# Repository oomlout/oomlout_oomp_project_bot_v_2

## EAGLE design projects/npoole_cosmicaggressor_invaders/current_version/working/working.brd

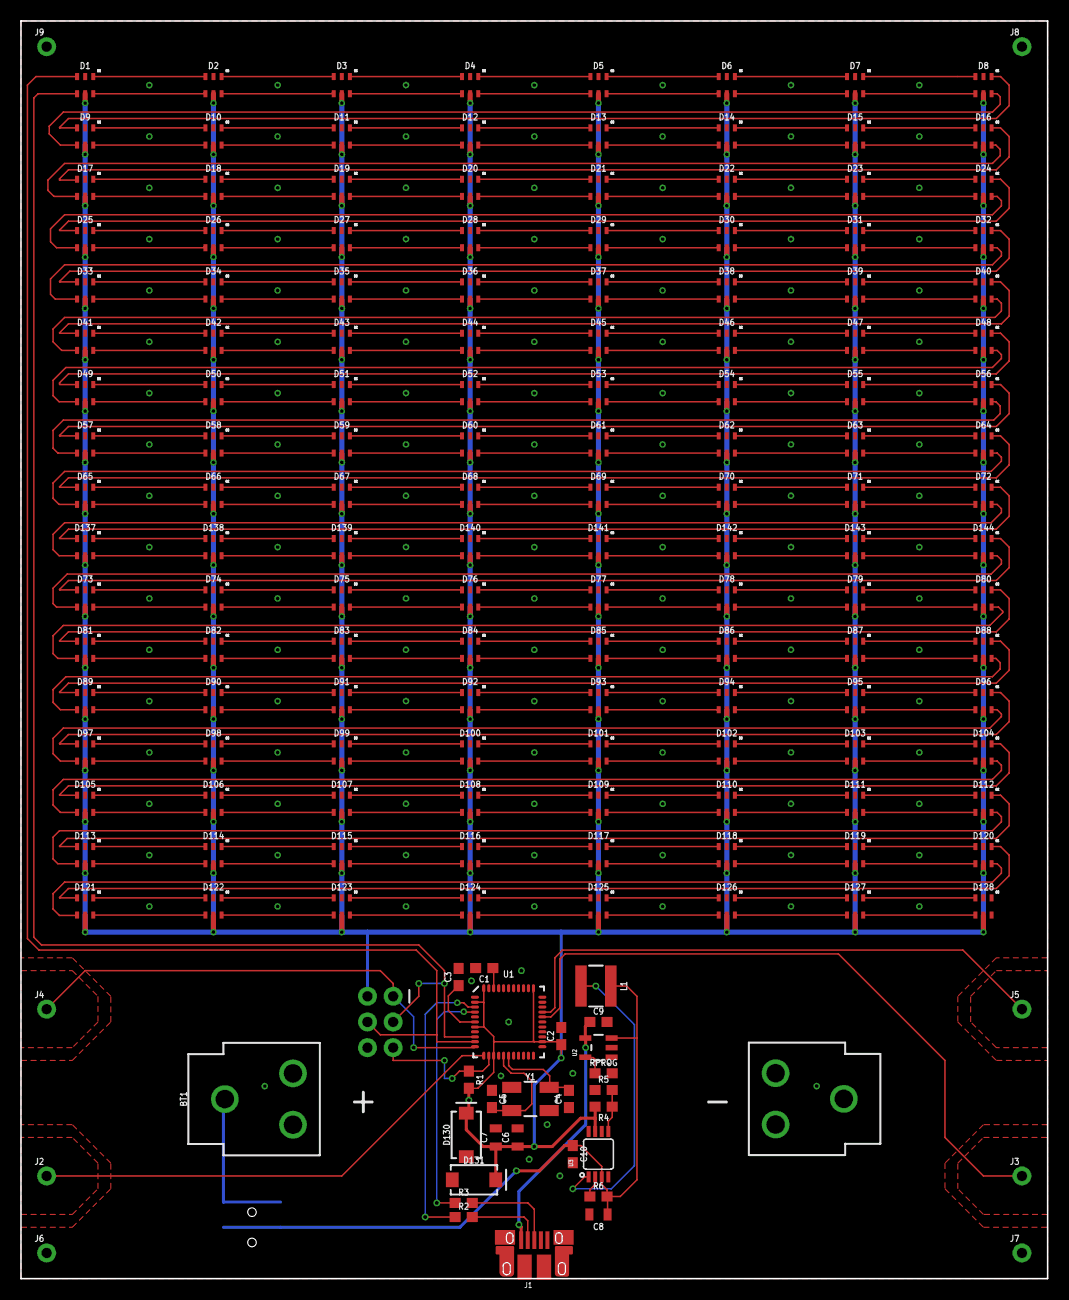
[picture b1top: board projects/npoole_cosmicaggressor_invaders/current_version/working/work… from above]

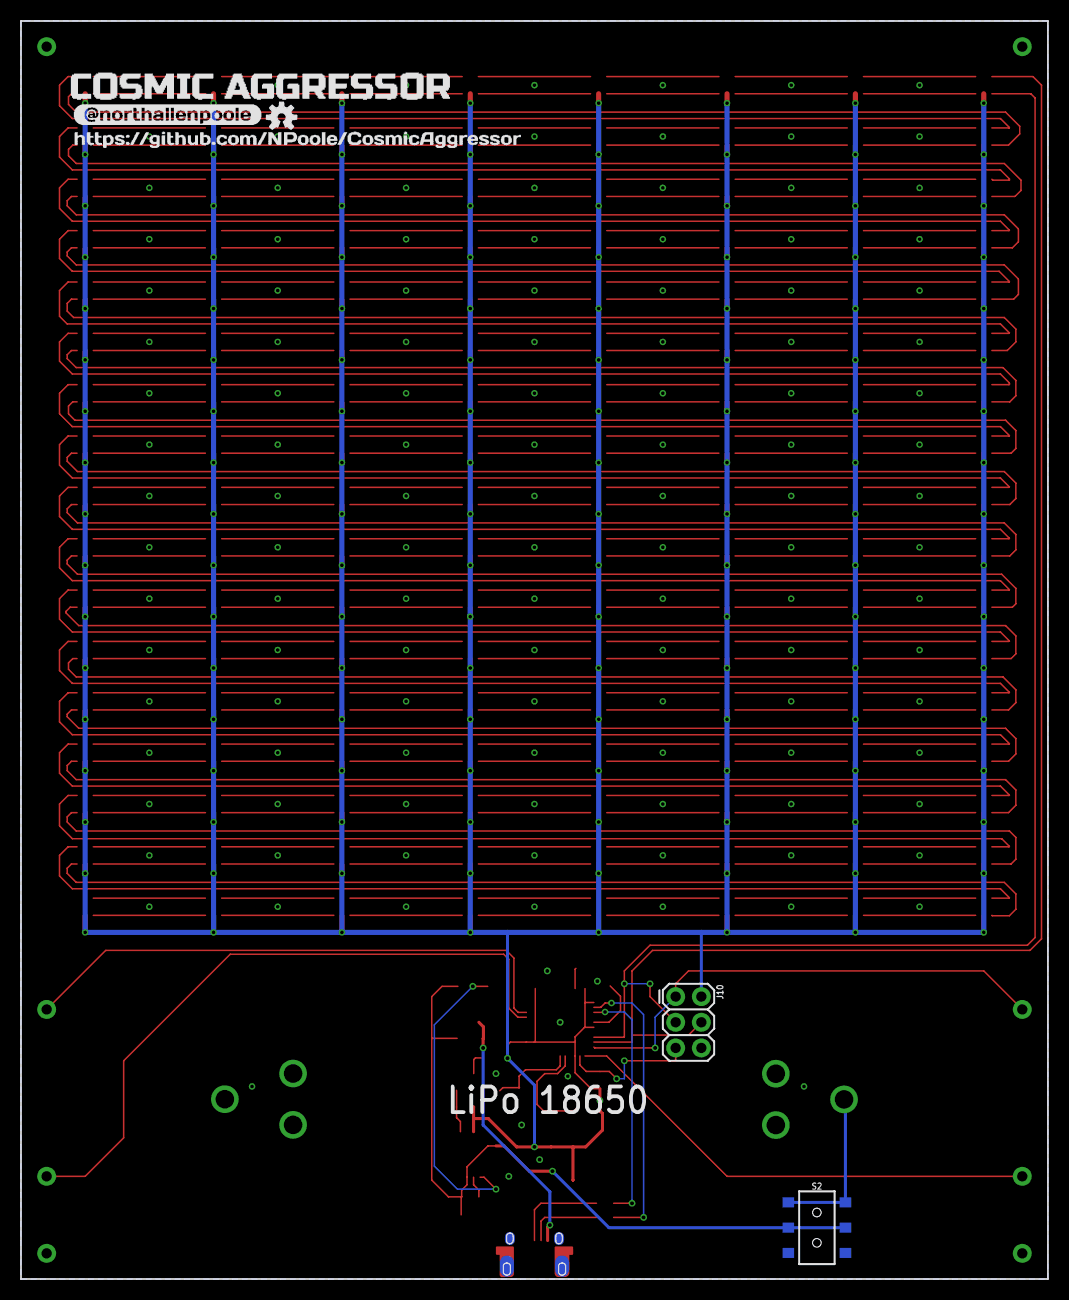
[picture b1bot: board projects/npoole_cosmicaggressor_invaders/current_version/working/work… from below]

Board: 2 copper layers, 101.6 x 124.5 mm, 176 parts (6 on the bottom side), 294 nets.

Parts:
BT1: BATTERY_18650-HOLDER
C1: 0.1uF; 0603
C2, C3: 1.0uF; 0603
C4, C5: 18pF; 0603
C6, C7, C8: 22uF; 0805
C9, C10: 4.7uF; 0603
D1, D2, D3, D4, D5, D6, D7, D8, D9, D10, D11, D12, D13, D14, D15, D16, D17, D18, D19, D20, D21, D22, D23, D24, D25, D26, D27, D28, D29, D30, D31, D32, D33, D34, D35, D36, D37, D38, D39, D40, D41, D42, D43, D44, D45, D46, D47, D48, D49, D50, D51, D52, D53, D54, D55, D56, D57, D58, D59, D60, D61, D62, D63, D64, D65, D66, D67, D68, D69, D70, D71, D72, D73, D74, D75, D76, D77, D78, D79, D80, D81, D82, D83, D84, D85, D86, D87, D88, D89, D90, D91, D92, D93, D94, D95, D96, D97, D98, D99, D100, D101, D102, D103, D104, D105, D106, D107, D108, D109, D110, D111, D112, D113, D114, D115, D116, D117, D118, D119, D120, D121, D122, D123, D124, D125, D126, D127, D128, D137, D138, D139, D140, D141, D142, D143, D144: APA102-2020
D130, D131: 3A/40V/500mV; SMA-DIODE
J1: USB-MICROB-PTH-MILL
J2, J3, J4, J5, J6, J7, J8, J9: 1X01NS_KIT
J10: AVR_SPI_PROG_3X2PTH; 2X3
L1: 2.2UH3A; INDUCTOR_4X4MM
R1: 10k; 0603@1
R2, R3: 22; 0603@1
R4, R6: 750K; 0603
R5: 100k; 0603
RPROG: 2.0k; 0603
S2: SWITCH_DPDT_SMD_AYZ0202
U1: 32U4; QFN-44-NOPAD_1:1-LESS_PASTE
U2: MCP73831; SOT23-5
U3: PAM2401; MSOP8
U$1: COSMIC_AGGRESSOR0
U$2: #NORTHALLENPOOLE1
U$3: HTTPS###GITHUB#COM#NPOOLE#COSMICAGGRESSOR2
U$4: OSHW-LOGO-S
Y1: 16MHz; CRYSTAL-SMD-5X3.2-4PAD

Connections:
5VIN: C9.1, J1.VBUS, U2.4
!RST: J10.5, R1.1, U1.13
D+: R3.1, U1.4
D-: R2.1, U1.3
EN: R6.1, U3.2
FIRE1: J2.1, U1.12
FIRE2: J3.1, U1.29
GND: BT1.GND@1, C1.2, C2.2, C3.2, C4.1, C5.1, C6.2, C7.2, C8.2, C9.2, C10.2, D1.GND, D2.GND, D3.GND, D4.GND, D5.GND, D6.GND, D7.GND, D8.GND, D9.GND, D10.GND, D11.GND, D12.GND, D13.GND, D14.GND, D15.GND, D16.GND, D17.GND, D18.GND, D19.GND, D20.GND, D21.GND, D22.GND, D23.GND, D24.GND, D25.GND, D26.GND, D27.GND, D28.GND, D29.GND, D30.GND, D31.GND, D32.GND, D33.GND, D34.GND, D35.GND, D36.GND, D37.GND, D38.GND, D39.GND, D40.GND, D41.GND, D42.GND, D43.GND, D44.GND, D45.GND, D46.GND, D47.GND, D48.GND, D49.GND, D50.GND, D51.GND, D52.GND, D53.GND, D54.GND, D55.GND, D56.GND, D57.GND, D58.GND, D59.GND, D60.GND, D61.GND, D62.GND, D63.GND, D64.GND, D65.GND, D66.GND, D67.GND, D68.GND, D69.GND, D70.GND, D71.GND, D72.GND, D73.GND, D74.GND, D75.GND, D76.GND, D77.GND, D78.GND, D79.GND, D80.GND, D81.GND, D82.GND, D83.GND, D84.GND, D85.GND, D86.GND, D87.GND, D88.GND, D89.GND, D90.GND, D91.GND, D92.GND, D93.GND, D94.GND, D95.GND, D96.GND, D97.GND, D98.GND, D99.GND, D100.GND, D101.GND, D102.GND, D103.GND, D104.GND, D105.GND, D106.GND, D107.GND, D108.GND, D109.GND, D110.GND, D111.GND, D112.GND, D113.GND, D114.GND, D115.GND, D116.GND, D117.GND, D118.GND, D119.GND, D120.GND, D121.GND, D122.GND, D123.GND, D124.GND, D125.GND, D126.GND, D127.GND, D128.GND, D130.A, D131.A, D137.GND, D138.GND, D139.GND, D140.GND, D141.GND, D142.GND, D143.GND, D144.GND, J1.GND, J1.SHIELD, J1.SHIELD2, J1.SHIELD3, J1.SHIELD4, J1.SHIELD5, J1.SHIELD6, J1.SHIELD7, J1.SHIELD8, J1.SHIELD9, J1.SHIELD10, J6.1, J7.1, J8.1, J9.1, J10.6, R5.1, RPROG.2, U1.5, U1.15, U1.23, U1.35, U1.43, U2.2, U3.4, U3.8
LEFT: J4.1, J10.1, U1.11
unnamed: D73.CKO, D74.CKI
unnamed: D73.SDO, D74.SDI
unnamed: D1.CKO, D2.CKI
unnamed: D1.SDO, D2.SDI
unnamed: D2.CKO, D3.CKI
unnamed: D2.SDO, D3.SDI
unnamed: D3.CKO, D4.CKI
unnamed: D3.SDO, D4.SDI
unnamed: D4.CKO, D5.CKI
unnamed: D4.SDO, D5.SDI
unnamed: D5.CKO, D6.CKI
unnamed: D5.SDO, D6.SDI
unnamed: D6.CKO, D7.CKI
unnamed: D6.SDO, D7.SDI
unnamed: D7.CKO, D8.CKI
unnamed: D7.SDO, D8.SDI
unnamed: D74.CKO, D75.CKI
unnamed: D74.SDO, D75.SDI
unnamed: D75.CKO, D76.CKI
unnamed: D75.SDO, D76.SDI
unnamed: D9.CKO, D10.CKI
unnamed: D9.SDO, D10.SDI
unnamed: D10.CKO, D11.CKI
unnamed: D10.SDO, D11.SDI
unnamed: D11.CKO, D12.CKI
unnamed: D11.SDO, D12.SDI
unnamed: D12.CKO, D13.CKI
unnamed: D12.SDO, D13.SDI
unnamed: D13.CKO, D14.CKI
unnamed: D13.SDO, D14.SDI
unnamed: D14.CKO, D15.CKI
unnamed: D14.SDO, D15.SDI
unnamed: D15.CKO, D16.CKI
unnamed: D15.SDO, D16.SDI
unnamed: D76.CKO, D77.CKI
unnamed: D76.SDO, D77.SDI
unnamed: D77.CKO, D78.CKI
unnamed: D77.SDO, D78.SDI
unnamed: D17.CKO, D18.CKI
unnamed: D17.SDO, D18.SDI
unnamed: D18.CKO, D19.CKI
unnamed: D18.SDO, D19.SDI
unnamed: D19.CKO, D20.CKI
unnamed: D19.SDO, D20.SDI
unnamed: D20.CKO, D21.CKI
unnamed: D20.SDO, D21.SDI
unnamed: D21.CKO, D22.CKI
unnamed: D21.SDO, D22.SDI
unnamed: D22.CKO, D23.CKI
unnamed: D22.SDO, D23.SDI
unnamed: D23.CKO, D24.CKI
unnamed: D23.SDO, D24.SDI
unnamed: D78.CKO, D79.CKI
unnamed: D78.SDO, D79.SDI
unnamed: D79.CKO, D80.CKI
unnamed: D79.SDO, D80.SDI
unnamed: D25.CKO, D26.CKI
unnamed: D25.SDO, D26.SDI
unnamed: D26.CKO, D27.CKI
unnamed: D26.SDO, D27.SDI
unnamed: D27.CKO, D28.CKI
unnamed: D27.SDO, D28.SDI
unnamed: D28.CKO, D29.CKI
unnamed: D28.SDO, D29.SDI
unnamed: D29.CKO, D30.CKI
unnamed: D29.SDO, D30.SDI
unnamed: D30.CKO, D31.CKI
unnamed: D30.SDO, D31.SDI
unnamed: D31.CKO, D32.CKI
unnamed: D31.SDO, D32.SDI
unnamed: D39.CKO, D40.CKI
unnamed: D39.SDO, D40.SDI
unnamed: D38.SDO, D39.SDI
unnamed: D38.CKO, D39.CKI
unnamed: D37.SDO, D38.SDI
unnamed: D37.CKO, D38.CKI
unnamed: D36.SDO, D37.SDI
unnamed: D36.CKO, D37.CKI
unnamed: D35.SDO, D36.SDI
unnamed: D35.CKO, D36.CKI
unnamed: D34.SDO, D35.SDI
unnamed: D34.CKO, D35.CKI
unnamed: D33.CKO, D34.CKI
unnamed: D33.SDO, D34.SDI
unnamed: D81.CKO, D82.CKI
unnamed: D81.SDO, D82.SDI
unnamed: D82.CKO, D83.CKI
unnamed: D82.SDO, D83.SDI
unnamed: D83.CKO, D84.CKI
unnamed: D83.SDO, D84.SDI
unnamed: D84.CKO, D85.CKI
unnamed: D84.SDO, D85.SDI
unnamed: D85.CKO, D86.CKI
unnamed: D85.SDO, D86.SDI
unnamed: D41.CKO, D42.CKI
unnamed: D41.SDO, D42.SDI
unnamed: D42.CKO, D43.CKI
unnamed: D42.SDO, D43.SDI
unnamed: D43.CKO, D44.CKI
unnamed: D43.SDO, D44.SDI
unnamed: D44.CKO, D45.CKI
unnamed: D44.SDO, D45.SDI
unnamed: D45.SDO, D46.SDI
unnamed: D45.CKO, D46.CKI
unnamed: D46.CKO, D47.CKI
unnamed: D46.SDO, D47.SDI
unnamed: D47.CKO, D48.CKI
unnamed: D47.SDO, D48.SDI
unnamed: D86.CKO, D87.CKI
unnamed: D86.SDO, D87.SDI
unnamed: D55.SDO, D56.SDI
unnamed: D55.CKO, D56.CKI
unnamed: D54.CKO, D55.CKI
unnamed: D54.SDO, D55.SDI
unnamed: D53.SDO, D54.SDI
unnamed: D53.CKO, D54.CKI
unnamed: D52.SDO, D53.SDI
unnamed: D52.CKO, D53.CKI
unnamed: D51.SDO, D52.SDI
unnamed: D51.CKO, D52.CKI
unnamed: D50.CKO, D51.CKI
unnamed: D50.SDO, D51.SDI
unnamed: D49.SDO, D50.SDI
unnamed: D49.CKO, D50.CKI
unnamed: D87.CKO, D88.CKI
unnamed: D87.SDO, D88.SDI
unnamed: D89.CKO, D90.CKI
unnamed: D89.SDO, D90.SDI
unnamed: D57.CKO, D58.CKI
unnamed: D57.SDO, D58.SDI
unnamed: D58.SDO, D59.SDI
unnamed: D58.CKO, D59.CKI
unnamed: D59.CKO, D60.CKI
unnamed: D59.SDO, D60.SDI
unnamed: D60.CKO, D61.CKI
unnamed: D60.SDO, D61.SDI
unnamed: D61.CKO, D62.CKI
unnamed: D61.SDO, D62.SDI
unnamed: D62.SDO, D63.SDI
unnamed: D62.CKO, D63.CKI
unnamed: D63.CKO, D64.CKI
unnamed: D63.SDO, D64.SDI
unnamed: D90.CKO, D91.CKI
unnamed: D90.SDO, D91.SDI
unnamed: D91.CKO, D92.CKI
unnamed: D91.SDO, D92.SDI
unnamed: D65.CKO, D66.CKI
unnamed: D65.SDO, D66.SDI
unnamed: D66.CKO, D67.CKI
unnamed: D66.SDO, D67.SDI
unnamed: D67.CKO, D68.CKI
unnamed: D67.SDO, D68.SDI
unnamed: D68.CKO, D69.CKI
unnamed: D68.SDO, D69.SDI
unnamed: D69.CKO, D70.CKI
unnamed: D69.SDO, D70.SDI
unnamed: D70.CKO, D71.CKI
unnamed: D70.SDO, D71.SDI
unnamed: D71.CKO, D72.CKI
unnamed: D71.SDO, D72.SDI
unnamed: D137.CKO, D138.CKI
unnamed: D137.SDO, D138.SDI
unnamed: D92.CKO, D93.CKI
unnamed: D92.SDO, D93.SDI
unnamed: D93.CKO, D94.CKI
unnamed: D93.SDO, D94.SDI
unnamed: D94.CKO, D95.CKI
unnamed: D94.SDO, D95.SDI
unnamed: D95.CKO, D96.CKI
unnamed: D95.SDO, D96.SDI
unnamed: D97.CKO, D98.CKI
unnamed: D97.SDO, D98.SDI
unnamed: D98.CKO, D99.CKI
unnamed: D98.SDO, D99.SDI
unnamed: D99.CKO, D100.CKI
unnamed: D99.SDO, D100.SDI
unnamed: D100.CKO, D101.CKI
unnamed: D100.SDO, D101.SDI
unnamed: D101.CKO, D102.CKI
unnamed: D101.SDO, D102.SDI
unnamed: D102.CKO, D103.CKI
unnamed: D102.SDO, D103.SDI
unnamed: D103.CKO, D104.CKI
unnamed: D103.SDO, D104.SDI
unnamed: D111.CKO, D112.CKI
unnamed: D111.SDO, D112.SDI
unnamed: D110.SDO, D111.SDI
unnamed: D110.CKO, D111.CKI
unnamed: D109.SDO, D110.SDI
unnamed: D109.CKO, D110.CKI
unnamed: D108.SDO, D109.SDI
unnamed: D108.CKO, D109.CKI
unnamed: D107.SDO, D108.SDI
unnamed: D107.CKO, D108.CKI
unnamed: D106.SDO, D107.SDI
unnamed: D106.CKO, D107.CKI
unnamed: D105.CKO, D106.CKI
unnamed: D105.SDO, D106.SDI
unnamed: D113.CKO, D114.CKI
unnamed: D113.SDO, D114.SDI
unnamed: D114.CKO, D115.CKI
unnamed: D114.SDO, D115.SDI
unnamed: D115.CKO, D116.CKI
unnamed: D115.SDO, D116.SDI
unnamed: D116.CKO, D117.CKI
unnamed: D116.SDO, D117.SDI
unnamed: D117.SDO, D118.SDI
unnamed: D117.CKO, D118.CKI
unnamed: D118.CKO, D119.CKI
unnamed: D118.SDO, D119.SDI
unnamed: D119.CKO, D120.CKI
unnamed: D119.SDO, D120.SDI
unnamed: D127.SDO, D128.SDI
unnamed: D127.CKO, D128.CKI
unnamed: D126.CKO, D127.CKI
unnamed: D126.SDO, D127.SDI
unnamed: D125.SDO, D126.SDI
unnamed: D125.CKO, D126.CKI
unnamed: D124.SDO, D125.SDI
unnamed: D124.CKO, D125.CKI
unnamed: D123.SDO, D124.SDI
unnamed: D123.CKO, D124.CKI
unnamed: D122.CKO, D123.CKI
unnamed: D122.SDO, D123.SDI
unnamed: D121.SDO, D122.SDI
unnamed: D121.CKO, D122.CKI
unnamed: C1.1, U1.42
unnamed: C4.2, U1.17, Y1.3
unnamed: C5.2, U1.16, Y1.1
unnamed: C3.1, U1.6
unnamed: RPROG.1, U2.5
unnamed: J1.D+, R3.2
unnamed: J1.D-, R2.2
unnamed: R4.1, R5.2, U3.5
unnamed: L1.P$2, U3.1
unnamed: BT1.PWR@1, S2.1, S2.4
unnamed: D138.CKO, D139.CKI
unnamed: D138.SDO, D139.SDI
unnamed: D139.CKO, D140.CKI
unnamed: D139.SDO, D140.SDI
unnamed: D140.CKO, D141.CKI
unnamed: D140.SDO, D141.SDI
unnamed: D141.CKO, D142.CKI
unnamed: D141.SDO, D142.SDI
unnamed: D142.CKO, D143.CKI
unnamed: D142.SDO, D143.SDI
unnamed: D143.CKO, D144.CKI
unnamed: D143.SDO, D144.SDI
R1CK: D1.CKI, J10.3, U1.9
R1DA: D1.SDI, J10.4, U1.10
R2CK: D8.CKO, D9.CKI
R2DA: D8.SDO, D9.SDI
R3CK: D16.CKO, D17.CKI
R3DA: D16.SDO, D17.SDI
R4CK: D24.CKO, D25.CKI
R4DA: D24.SDO, D25.SDI
R5CK: D32.CKO, D33.CKI
R5DA: D32.SDO, D33.SDI
R6CK: D40.CKO, D41.CKI
R6DA: D40.SDO, D41.SDI
R7CK: D48.CKO, D49.CKI
R7DA: D48.SDO, D49.SDI
R8CK: D56.CKO, D57.CKI
R8DA: D56.SDO, D57.SDI
R9CK: D64.CKO, D65.CKI
R9DA: D64.SDO, D65.SDI
R10CK: D72.CKO, D137.CKI
R10DA: D72.SDO, D137.SDI
R11CK: D73.CKI, D144.CKO
R11DA: D73.SDI, D144.SDO
R12CK: D80.CKO, D81.CKI
R12DA: D80.SDO, D81.SDI
R13CK: D88.CKO, D89.CKI
R13DA: D88.SDO, D89.SDI
R14CK: D96.CKO, D97.CKI
R14DA: D96.SDO, D97.SDI
R15CK: D104.CKO, D105.CKI
R15DA: D104.SDO, D105.SDI
R16CK: D112.CKO, D113.CKI
R16DA: D112.SDO, D113.SDI
R17CK: D120.CKO, D121.CKI
R17DA: D120.SDO, D121.SDI
RIGHT: J5.1, U1.30
VBATT: C8.1, C10.1, L1.P$1, R6.2, S2.2, S2.5, U2.3, U3.3
VCC: C2.1, C6.1, C7.1, D1.VDD, D2.VDD, D3.VDD, D4.VDD, D5.VDD, D6.VDD, D7.VDD, D8.VDD, D9.VDD, D10.VDD, D11.VDD, D12.VDD, D13.VDD, D14.VDD, D15.VDD, D16.VDD, D17.VDD, D18.VDD, D19.VDD, D20.VDD, D21.VDD, D22.VDD, D23.VDD, D24.VDD, D25.VDD, D26.VDD, D27.VDD, D28.VDD, D29.VDD, D30.VDD, D31.VDD, D32.VDD, D33.VDD, D34.VDD, D35.VDD, D36.VDD, D37.VDD, D38.VDD, D39.VDD, D40.VDD, D41.VDD, D42.VDD, D43.VDD, D44.VDD, D45.VDD, D46.VDD, D47.VDD, D48.VDD, D49.VDD, D50.VDD, D51.VDD, D52.VDD, D53.VDD, D54.VDD, D55.VDD, D56.VDD, D57.VDD, D58.VDD, D59.VDD, D60.VDD, D61.VDD, D62.VDD, D63.VDD, D64.VDD, D65.VDD, D66.VDD, D67.VDD, D68.VDD, D69.VDD, D70.VDD, D71.VDD, D72.VDD, D73.VDD, D74.VDD, D75.VDD, D76.VDD, D77.VDD, D78.VDD, D79.VDD, D80.VDD, D81.VDD, D82.VDD, D83.VDD, D84.VDD, D85.VDD, D86.VDD, D87.VDD, D88.VDD, D89.VDD, D90.VDD, D91.VDD, D92.VDD, D93.VDD, D94.VDD, D95.VDD, D96.VDD, D97.VDD, D98.VDD, D99.VDD, D100.VDD, D101.VDD, D102.VDD, D103.VDD, D104.VDD, D105.VDD, D106.VDD, D107.VDD, D108.VDD, D109.VDD, D110.VDD, D111.VDD, D112.VDD, D113.VDD, D114.VDD, D115.VDD, D116.VDD, D117.VDD, D118.VDD, D119.VDD, D120.VDD, D121.VDD, D122.VDD, D123.VDD, D124.VDD, D125.VDD, D126.VDD, D127.VDD, D128.VDD, D130.C, D131.C, D137.VDD, D138.VDD, D139.VDD, D140.VDD, D141.VDD, D142.VDD, D143.VDD, D144.VDD, J10.2, R1.2, R4.2, U1.2, U1.7, U1.14, U1.24, U1.34, U1.44, U3.7

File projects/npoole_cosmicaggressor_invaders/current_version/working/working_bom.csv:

"Id";"Designator";"Footprint";"Quantity";"Designation";"Supplier and ref";
1;"D72,D84,D8,D46,D67,D22,D29,D92,D126,D20,D68,D66,D52,D87,D108,D99,D95,D2,D57,D100,D127,D120,D117,D38,D102,D137,D31,D61,D17,D3,D65,D121,D37,D30,D85,D103,D98,D33,D140,D79,D41,D1,D81,D77,D40,D11,D75,D19,D47,D74,D62,D49,D93,D128,D109,D141,D143,D42,D56,D54,D71,D115,D78,D111,D124,D114,D110,D50,D144,D24,D26,D5,D107,D35,D4,D76,D43,D28,D7,D104,D45,D101,D63,D90,D122,D60,D51,D15,D55,D16,D116,D48,D39,D80,D34,D23,D32,D123,D112,D12,D96,D105,D10,D142,D58,D113,D9,D25,D125,D106,D94,D53,D86,D139,D36,D118,D18,D44,D13,D64,D73,D59,D138,D69,D21,D6,D27,D82,D70,D119,D91,D89,D97,D88,D83,D14";"APA102-2020";136;"APA102-2020";;;
2;"C9,C10";"0603";2;"4.7uF";;;
3;"U2";"SOT23-5";1;"MCP73831";;;
4;"R3,R2";"0603@1";2;"22";;;
5;"Y1";"CRYSTAL-SMD-5X3.2-4PAD";1;"16MHz";;;
6;"R1";"0603@1";1;"10k";;;
7;"BT1";"BATTERY_18650-HOLDER";1;"";;;
8;"J9,J6,J5,J8,J4,J7,J2,J3";"1X01NS_KIT";8;"";;;
9;"D131,D130";"SMA-DIODE";2;"3A/40V/500mV";;;
10;"C2,C3";"0603";2;"1.0uF";;;
11;"C8,C6,C7";"0805";3;"22uF";;;
12;"C4,C5";"0603";2;"18pF";;;
13;"R6,R4";"0603";2;"750K";;;
14;"RPROG0";"0603";1;"2.0k";;;
15;"R5";"0603";1;"100k";;;
16;"C1";"0603";1;"0.1uF";;;
17;"U3";"MSOP8";1;"PAM2401";;;
18;"L1";"INDUCTOR_4X4MM";1;"2.2UH3A";;;
19;"J1";"USB-MICROB-PTH-MILL";1;"";;;
20;"U1";"QFN-44-NOPAD_1_1-LESS_PASTE";1;"32U4";;;
21;"S2";"SWITCH_DPDT_SMD_AYZ0202";1;"";;;
22;"U$1";"COSMIC_AGGRESSOR0";1;"";;;
23;"J10";"2X3";1;"AVR_SPI_PROG_3X2PTH";;;
24;"U$2";"#NORTHALLENPOOLE1";1;"";;;
25;"U$4";"OSHW-LOGO-S";1;"";;;
26;"U$3";"HTTPS###GITHUB#COM#NPOOLE#COSMICAGGRESSOR2";1;"";;;

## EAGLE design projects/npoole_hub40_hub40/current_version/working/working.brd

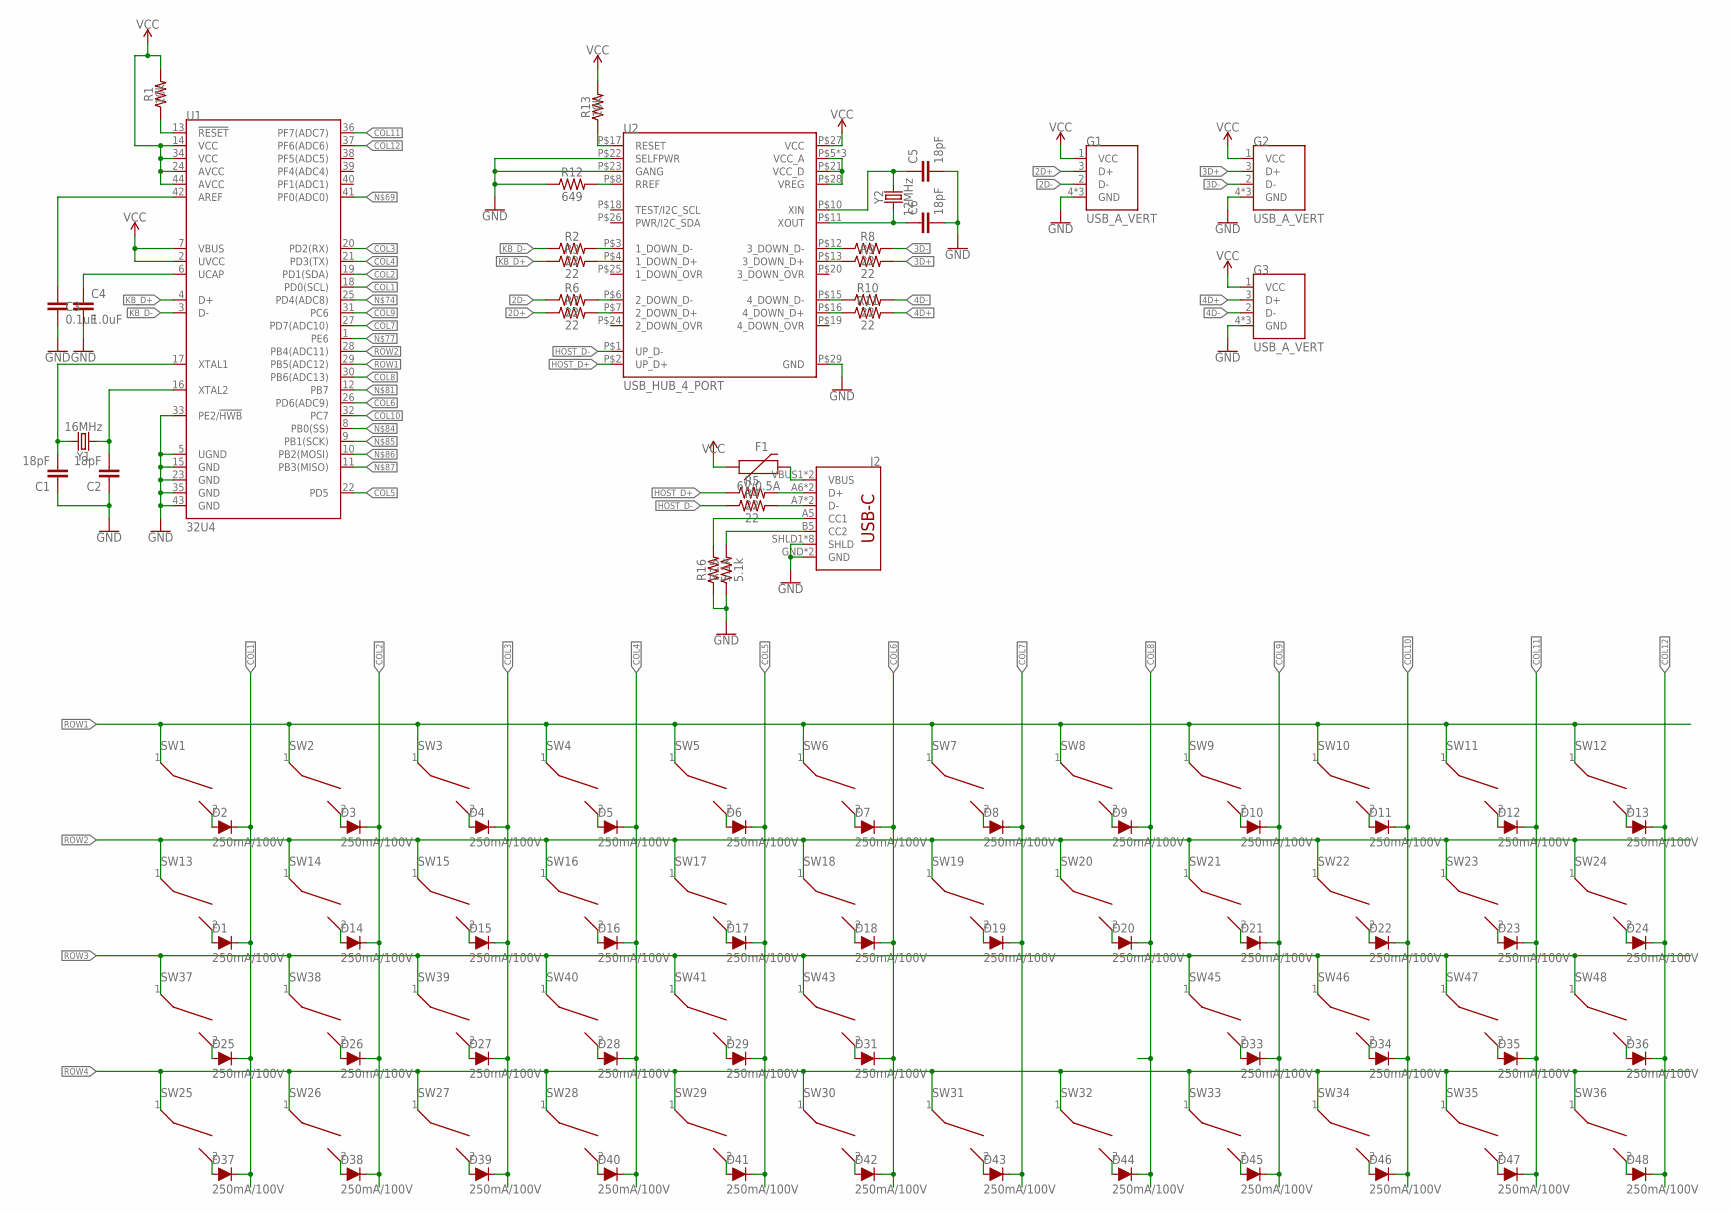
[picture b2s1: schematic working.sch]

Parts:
C1, C2, C5, C6: 18pF; 0603
C3: 0.1uF; 0603
C4: 1.0uF; 0603
D1, D2, D3, D4, D5, D6, D7, D8, D9, D10, D11, D12, D13, D14, D15, D16, D17, D18, D19, D20, D21, D22, D23, D24, D25, D26, D27, D28, D29, D31, D33, D34, D35, D36, D37, D38, D39, D40, D41, D42, D43, D44, D45, D46, D47, D48: 250mA/100V; SOD-323
F1: 6V/0.5A; 1206
G1, G2, G3: USB_A_VERT
J2: USB_C2-LAYER; USB-C-16P
R1, R13: 10k; 0603
R2, R3, R4, R5, R6, R7, R8, R9, R10, R11: 22; 0603
R12: 649; 0603
R15, R16: 5.1k; 0603
SW1, SW2, SW3, SW4, SW5, SW6, SW7, SW8, SW9, SW10, SW11, SW12, SW13, SW14, SW15, SW16, SW17, SW18, SW19, SW20, SW21, SW22, SW23, SW24, SW25, SW26, SW27, SW28, SW29, SW30, SW31, SW32, SW33, SW34, SW35, SW36, SW37, SW38, SW39, SW40, SW41, SW43, SW45, SW46, SW47, SW48: CHERRY_MX_WITH_FIXING_PINS; MX1A-XXNW
U1: 32U4; QFN-44-NOPAD_1:1
U2: USB_HUB_4_PORT; QFN-28-5MM-1:1
Y1: 16MHz; CRYSTAL-SMD-5X3.2-4PAD
Y2: 12MHz; CRYSTAL-SMD-5X3.2-4PAD

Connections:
2D+: G1.3 (D+), R7.1
2D-: G1.2 (D-), R6.1
3D+: G2.3 (D+), R9.2
3D-: G2.2 (D-), R8.2
4D+: G3.3 (D+), R11.2
4D-: G3.2 (D-), R10.2
COL1: D1.C, D2.C, D25.C, D37.C, U1.18 (PD0(SCL))
COL2: D3.C, D14.C, D26.C, D38.C, U1.19 (PD1(SDA))
COL3: D4.C, D15.C, D27.C, D39.C, U1.20 (PD2(RX))
COL4: D5.C, D16.C, D28.C, D40.C, U1.21 (PD3(TX))
COL5: D6.C, D17.C, D29.C, D41.C, U1.22 (PD5)
COL6: D7.C, D18.C, D31.C, D42.C, U1.26 (PD6(ADC9))
COL7: D8.C, D19.C, D43.C, U1.27 (PD7(ADC10))
COL8: D9.C, D20.C, D44.C, U1.30 (PB6(ADC13))
COL9: D10.C, D21.C, D33.C, D45.C, U1.31 (PC6)
COL10: D11.C, D22.C, D34.C, D46.C, U1.32 (PC7)
COL11: D12.C, D23.C, D35.C, D47.C, U1.36 (PF7(ADC7))
COL12: D13.C, D24.C, D36.C, D48.C, U1.37 (PF6(ADC6))
GND: C1.1, C2.1, C3.2, C4.2, C5.2, C6.2, G1.4 (GND), G1.SHIELD_1 (GND), G1.SHIELD_2 (GND), G2.4 (GND), G2.SHIELD_1 (GND), G2.SHIELD_2 (GND), G3.4 (GND), G3.SHIELD_1 (GND), G3.SHIELD_2 (GND), J2.GND, J2.GND2 (GND), J2.SHLD1 (SHLD), J2.SHLD2 (SHLD), J2.SHLD3 (SHLD), J2.SHLD4 (SHLD), J2.SHLD5 (SHLD), J2.SHLD6 (SHLD), J2.SHLD7 (SHLD), J2.SHLD8 (SHLD), R12.1, R15.1, R16.1, U1.5 (UGND), U1.15 (GND), U1.23 (GND), U1.33 (PE2/!HWB), U1.35 (GND), U1.43 (GND), U2.P$22 (SELFPWR), U2.P$23 (GANG), U2.P$29 (GND)
HOST-: J2.A7 (D-), J2.B7 (D-), R4.2
HOST_D+: R5.1, U2.P$2 (UP_D+)
HOST_D-: R4.1, U2.P$1 (UP_D-)
KBD+: R3.2, U2.P$4 (1_DOWN_D+)
KBD-: R2.2, U2.P$3 (1_DOWN_D-)
KB_D+: R3.1, U1.4 (D+)
KB_D-: R2.1, U1.3 (D-)
unnamed: D2.A, SW1.2
unnamed: D3.A, SW2.2
unnamed: D4.A, SW3.2
unnamed: D5.A, SW4.2
unnamed: D6.A, SW5.2
unnamed: D7.A, SW6.2
unnamed: D8.A, SW7.2
unnamed: D9.A, SW8.2
unnamed: D10.A, SW9.2
unnamed: D11.A, SW10.2
unnamed: D12.A, SW11.2
unnamed: D13.A, SW12.2
unnamed: D1.A, SW13.2
unnamed: D25.A, SW37.2
unnamed: D37.A, SW25.2
unnamed: D38.A, SW26.2
unnamed: D26.A, SW38.2
unnamed: D14.A, SW14.2
unnamed: D15.A, SW15.2
unnamed: D16.A, SW16.2
unnamed: D28.A, SW40.2
unnamed: D27.A, SW39.2
unnamed: D39.A, SW27.2
unnamed: D40.A, SW28.2
unnamed: D41.A, SW29.2
unnamed: D42.A, SW30.2
unnamed: D29.A, SW41.2
unnamed: D17.A, SW17.2
unnamed: D18.A, SW18.2
unnamed: J2.A6 (D+), J2.B6 (D+), R5.2
unnamed: D43.A, SW31.2
unnamed: D31.A, SW43.2
unnamed: D19.A, SW19.2
unnamed: D23.A, SW23.2
unnamed: D22.A, SW22.2
unnamed: D21.A, SW21.2
unnamed: D20.A, SW20.2
unnamed: J2.A5 (CC1), R16.2
unnamed: D33.A, SW45.2
unnamed: D34.A, SW46.2
unnamed: D35.A, SW47.2
unnamed: D36.A, SW48.2
unnamed: D24.A, SW24.2
unnamed: D48.A, SW36.2
unnamed: D47.A, SW35.2
unnamed: D46.A, SW34.2
unnamed: D45.A, SW33.2
unnamed: D44.A, SW32.2
unnamed: R1.1, U1.13 (!RESET)
unnamed: C3.1, U1.42 (AREF)
unnamed: C1.2, U1.17 (XTAL1), Y1.3 (2)
unnamed: C2.2, U1.16 (XTAL2), Y1.1
unnamed: C4.1, U1.6 (UCAP)
unnamed: R6.2, U2.P$6 (2_DOWN_D-)
unnamed: U2.P$5 (VCC_A), U2.P$9 (VCC_A), U2.P$14 (VCC_A), U2.P$21 (VCC_D), U2.P$28 (VREG)
unnamed: R7.2, U2.P$7 (2_DOWN_D+)
unnamed: R8.1, U2.P$12 (3_DOWN_D-)
unnamed: R9.1, U2.P$13 (3_DOWN_D+)
unnamed: R10.1, U2.P$15 (4_DOWN_D-)
unnamed: R11.1, U2.P$16 (4_DOWN_D+)
unnamed: C5.1, U2.P$10 (XIN), Y2.3 (2)
unnamed: C6.1, U2.P$11 (XOUT), Y2.1
unnamed: R13.1, U2.P$17 (RESET)
unnamed: F1.2, J2.VBUS1 (VBUS), J2.VBUS2 (VBUS)
unnamed: R12.2, U2.P$8 (RREF)
unnamed: J2.B5 (CC2), R15.2
ROW1: SW1.1, SW2.1, SW3.1, SW4.1, SW5.1, SW6.1, SW7.1, SW8.1, SW9.1, SW10.1, SW11.1, SW12.1, U1.29 (PB5(ADC12))
ROW2: SW13.1, SW14.1, SW15.1, SW16.1, SW17.1, SW18.1, SW19.1, SW20.1, SW21.1, SW22.1, SW23.1, SW24.1, U1.28 (PB4(ADC11))
ROW3: SW37.1, SW38.1, SW39.1, SW40.1, SW41.1, SW43.1, SW45.1, SW46.1, SW47.1, SW48.1
ROW4: SW25.1, SW26.1, SW27.1, SW28.1, SW29.1, SW30.1, SW31.1, SW32.1, SW33.1, SW34.1, SW35.1, SW36.1
VCC: F1.1, G1.1 (VCC), G2.1 (VCC), G3.1 (VCC), R1.2, R13.2, U1.2 (UVCC), U1.7 (VBUS), U1.14 (VCC), U1.24 (AVCC), U1.34 (VCC), U1.44 (AVCC), U2.P$27 (VCC)

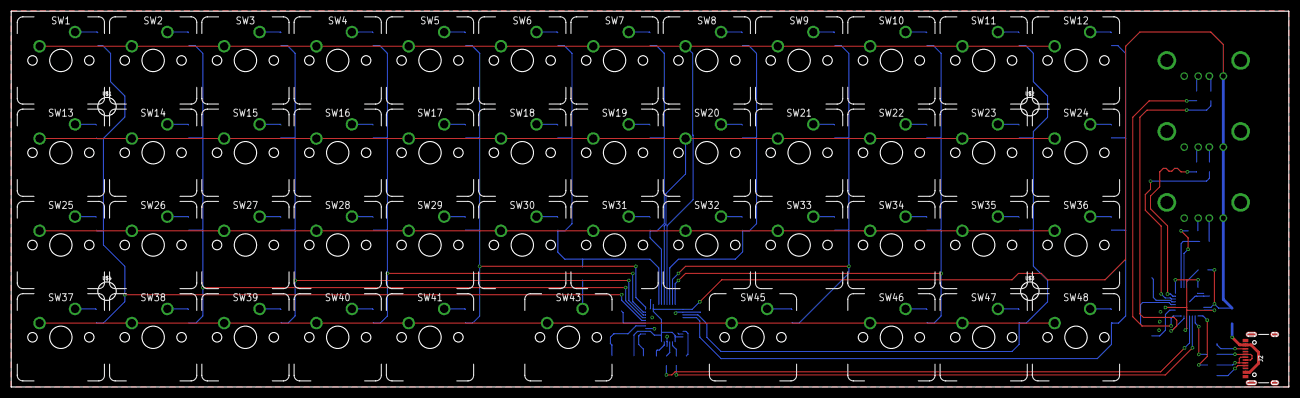
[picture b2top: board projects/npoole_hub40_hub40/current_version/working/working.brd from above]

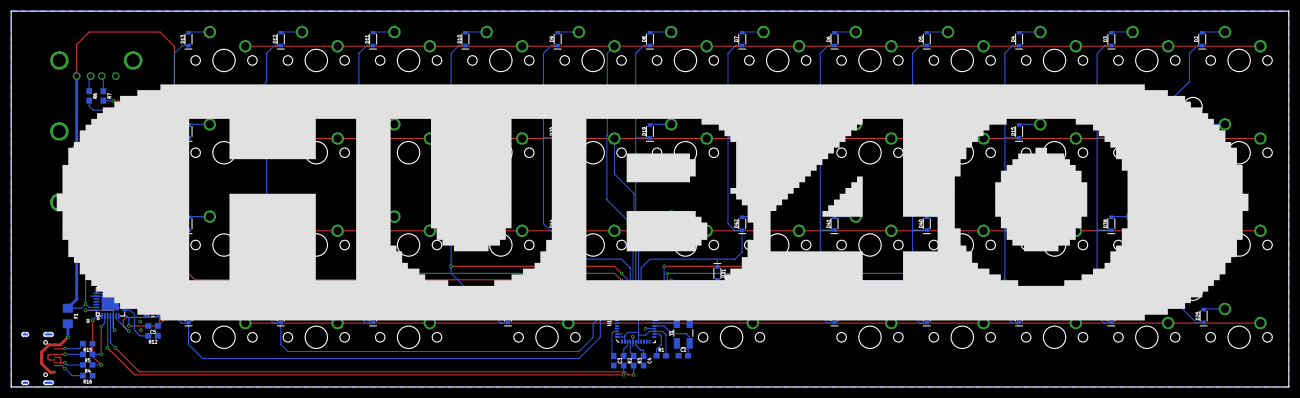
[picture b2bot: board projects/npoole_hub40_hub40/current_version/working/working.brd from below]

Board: 2 copper layers, 228.6 x 67.2 mm, 127 parts (73 on the bottom side), 97 nets.

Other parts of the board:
U$1, U$2, U$3, U$4: STAND-OFF
U$5: HUB400

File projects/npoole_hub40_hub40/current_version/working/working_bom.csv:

"Id";"Designator";"Footprint";"Quantity";"Designation";"Supplier and ref";
1;"SW37,SW31,SW19,SW24,SW6,SW15,SW25,SW18,SW5,SW23,SW46,SW39,SW30,SW22,SW26,SW38,SW48,SW43,SW8,SW28,SW33,SW16,SW35,SW17,SW4,SW20,SW10,SW34,SW29,SW21,SW41,SW13,SW40,SW11,SW7,SW2,SW14,SW36,SW12,SW32,SW47,SW1,SW45,SW3,SW9,SW27";"MX1A-XXNW";46;"";;;
2;"G1,G3,G2";"USB_A_VERT";3;"USB_A_VERT";;;
3;"U$3,U$1,U$4,U$2";"STAND-OFF";4;"";;;
4;"J2";"USB-C-16P";1;"";;;
5;"D12,D21,D37,D26,D2,D34,D22,D45,D5,D15,D36,D29,D39,D19,D47,D17,D10,D8,D44,D1,D23,D42,D18,D48,D9,D27,D16,D20,D43,D24,D3,D41,D6,D13,D38,D25,D28,D40,D4,D35,D11,D31,D46,D7,D14,D33";"SOD-323";46;"250mA/100V";;;
6;"R7,R8,R3,R2,R10,R5,R4,R6,R11,R9";"0603";10;"22";;;
7;"R1,R13";"0603";2;"10k";;;
8;"U2";"QFN-28-5MM-1_1";1;"USB_HUB_4_PORT";;;
9;"R16,R15";"0603";2;"5.1k";;;
10;"C2,C6,C1,C5";"0603";4;"18pF";;;
11;"U1";"QFN-44-NOPAD_1_1";1;"32U4";;;
12;"Y2";"CRYSTAL-SMD-5X3.2-4PAD";1;"12MHz";;;
13;"R12";"0603";1;"649";;;
14;"F1";"1206";1;"6V/0.5A";;;
15;"Y1";"CRYSTAL-SMD-5X3.2-4PAD";1;"16MHz";;;
16;"C4";"0603";1;"1.0uF";;;
17;"C3";"0603";1;"0.1uF";;;
18;"U$5";"HUB400";1;"";;;

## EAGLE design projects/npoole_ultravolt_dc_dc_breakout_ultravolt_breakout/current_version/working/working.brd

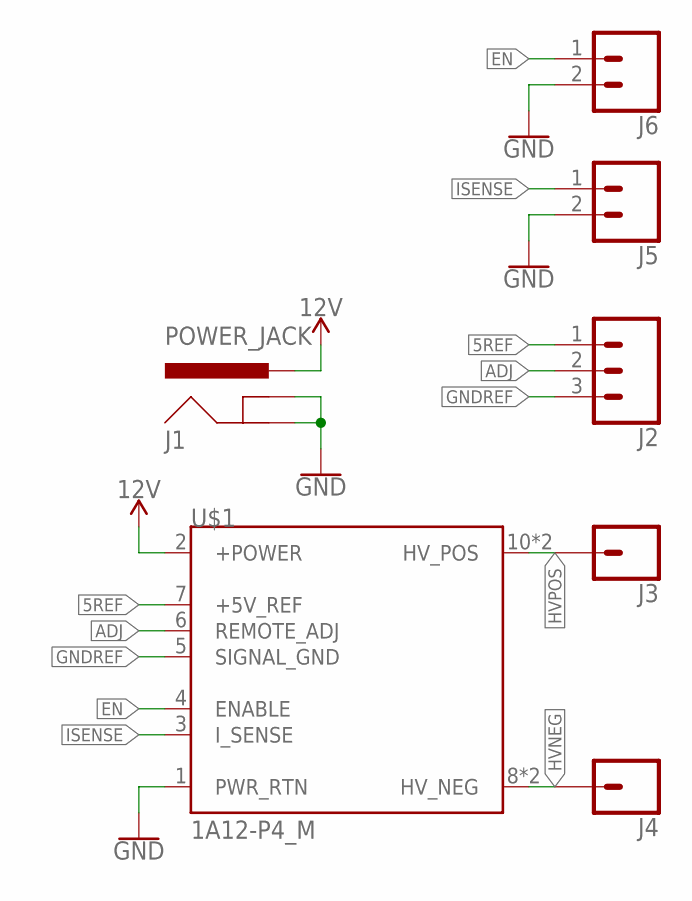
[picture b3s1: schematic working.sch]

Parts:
J1: POWER_JACK; POWER_JACK_PTH
J2: CONN_031X03_NO_SILK; 1X03_NO_SILK
J3, J4: CONN_01PTH_2MM; 1X01_2MM
J5, J6: CONN_021X02_NO_SILK; 1X02_NO_SILK
U$1: 1A12-P4_M; ULTRAVOLT

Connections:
5REF: J2.1, U$1.7 (+5V_REF)
12V: J1.PWR, U$1.2 (+POWER)
ADJ: J2.2, U$1.6 (REMOTE_ADJ)
EN: J6.1, U$1.4 (ENABLE)
GND: J1.GND, J1.GNDBREAK, J5.2, J6.2, U$1.1 (PWR_RTN)
GNDREF: J2.3, U$1.5 (SIGNAL_GND)
HVNEG: J4.1, U$1.8 (HV_NEG), U$1.9 (HV_NEG)
HVPOS: J3.1, U$1.10 (HV_POS), U$1.11 (HV_POS)
ISENSE: J5.1, U$1.3 (I_SENSE)

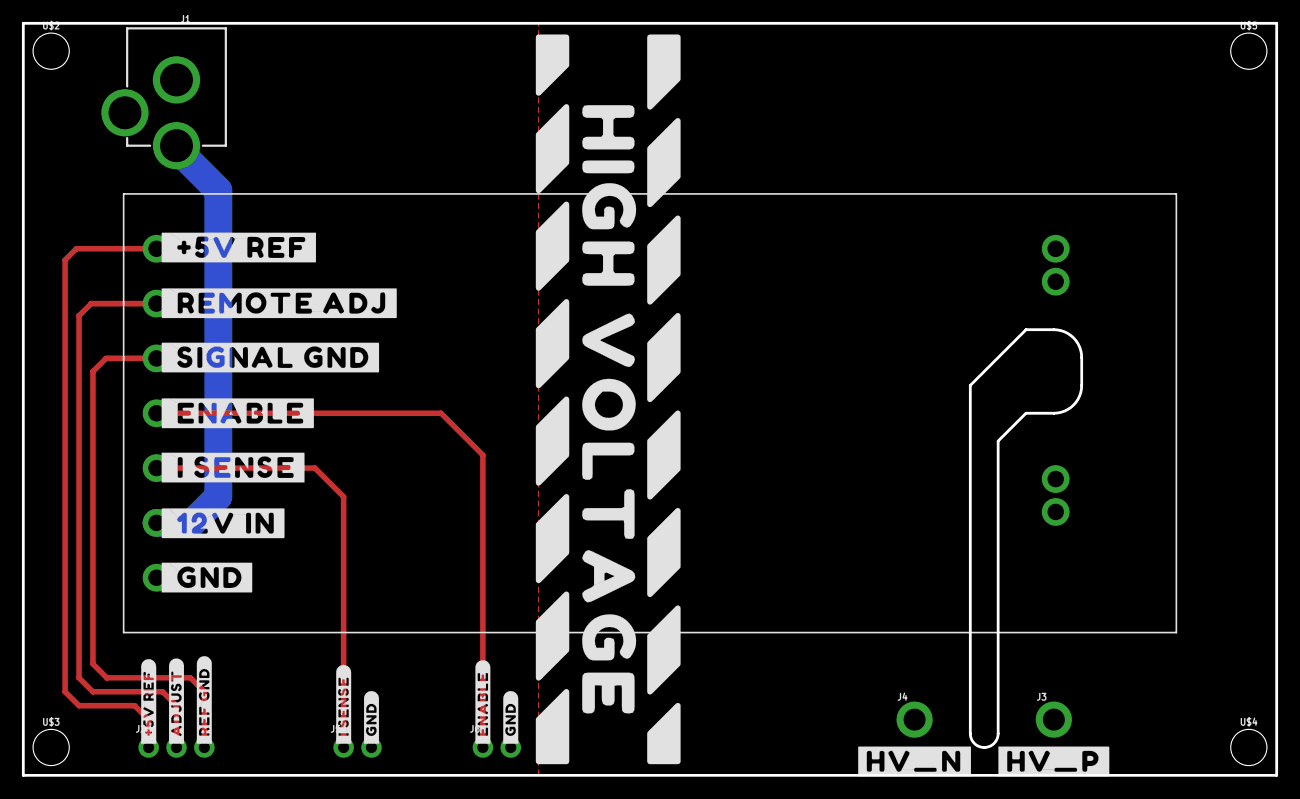
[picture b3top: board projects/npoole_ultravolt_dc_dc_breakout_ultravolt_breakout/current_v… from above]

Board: 2 copper layers, 114.3 x 68.6 mm, 28 parts (0 on the bottom side), 9 nets.

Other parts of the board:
U$2, U$3, U$4, U$5: STAND-OFF
U$6: HIGH_VOLTAGE0
U$7: #_#5V_REF#0
U$8: #_REMOTE_ADJ#0
U$9: #_SIGNAL_GND#0
U$10: #_ENABLE#0
U$11: #_I_SENSE#0
U$12: #_12V_IN#0
U$13: #_GND#0
U$14: #_#5V_REF_#0
U$15: #_ADJUST_#0
U$16: #HV_N#0
U$17: #HV_P#0
U$18: #_REF_GND_#0
U$19: #_I_SENSE_#0
U$20: #_ENABLE_#0
U$21, U$22: #_GND_#0

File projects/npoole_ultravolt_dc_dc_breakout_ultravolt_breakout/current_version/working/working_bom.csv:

"Id";"Designator";"Footprint";"Quantity";"Designation";"Supplier and ref";
1;"U$1";"ULTRAVOLT";1;"1A12-P4_M";;;
2;"U$21,U$22";"#_GND_#0";2;"";;;
3;"U$12";"#_12V_IN#0";1;"";;;
4;"J3,J4";"1X01_2MM";2;"";;;
5;"U$14";"#_#5V_REF_#0";1;"";;;
6;"J2";"1X03_NO_SILK";1;"";;;
7;"U$13";"#_GND#0";1;"";;;
8;"U$20";"#_ENABLE_#0";1;"";;;
9;"U$3,U$4,U$2,U$5";"STAND-OFF";4;"";;;
10;"U$7";"#_#5V_REF#0";1;"";;;
11;"U$17";"#HV_P#0";1;"";;;
12;"J1";"POWER_JACK_PTH";1;"POWER_JACK";;;
13;"U$8";"#_REMOTE_ADJ#0";1;"";;;
14;"U$19";"#_I_SENSE_#0";1;"";;;
15;"U$10";"#_ENABLE#0";1;"";;;
16;"U$15";"#_ADJUST_#0";1;"";;;
17;"U$11";"#_I_SENSE#0";1;"";;;
18;"U$16";"#HV_N#0";1;"";;;
19;"J5,J6";"1X02_NO_SILK";2;"";;;
20;"U$9";"#_SIGNAL_GND#0";1;"";;;
21;"U$6";"HIGH_VOLTAGE0";1;"";;;
22;"U$18";"#_REF_GND_#0";1;"";;;

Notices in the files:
parts and their libraries:
SparkFun-LED: Licensing: Creative Commons ShareAlike 4.0 International - https://creativecommons.org/licenses/by-sa/4.0
COPYRIGHT: Copyright (C) 2021 Ultra Librarian. All rights reserved.
SparkFun-Aesthetics: Released under the Creative Commons Attribution Share-Alike 4.0 License
